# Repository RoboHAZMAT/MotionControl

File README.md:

Motion Control
=============

Code for the intuitive motion control for the robot. This repo contains all of the code needed to use the wearable motion control interface. Main features are the Motion Control Glove code and the IMU sensor reading programs.

###**Directories:**

  - **HandMotionControlOpt:** An optimized version of the code needed to operate the robot hands using the flex sensor based gloves. Takes the voltage drop readings from the flex sensor in the analog pins and relates that to servo motor rotation angles. Has a calibration method for different sized hands with a default setting as well. Green, yellow, and red LED status lights are used. Written for an Arduino Lilypad.

  - **IMUReading:** Contains several library files developed by Jeff Rowberg to deal with reading in the MPU 9150 IMU sensor we are using as well as the DMP. Two versions of IMU reading programs are functional, one which uses the DMP and one that uses the raw gyroscope and accelerometer data along with our custom Kalman Filter.
  
  - **Kalman Filter MATLAB:** Old code written for Dr. Tomonari Furukawa's Bayesian Robotics course implementing a one DOF Kalman Filter for accurate yaw estimates and drift cancelling.
  
  - **Mechtronic Arm:** In progress directory for controlling the Mechatronic Arm in various ways for testing.
  
  - **Tactile Feedback:** In progress directory used for tactile feedback code. The plan is to use a pressure sensor at the tips of the gripper fingers that senses when the gripper is touching an object. The pressure is related so some sort of tactile feedback method, either small inflatable pressure bags on the glove fingers or small vibration motors. 
  
  - **I2CDev:** Added standard library for communication over I2C on Arduino.

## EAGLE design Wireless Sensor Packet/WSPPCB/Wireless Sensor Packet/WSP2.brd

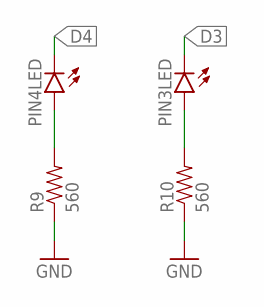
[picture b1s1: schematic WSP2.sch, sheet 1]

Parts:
PIN3LED, PIN4LED: LED0603; LED-0603
R9, R10: 560; 0603-RES

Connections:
D3: PIN3LED.C; also elsewhere on the board
D4: PIN4LED.C; also elsewhere on the board
GND: R9.1, R10.1; also elsewhere on the board
unnamed: PIN4LED.A, R9.2
unnamed: PIN3LED.A, R10.2

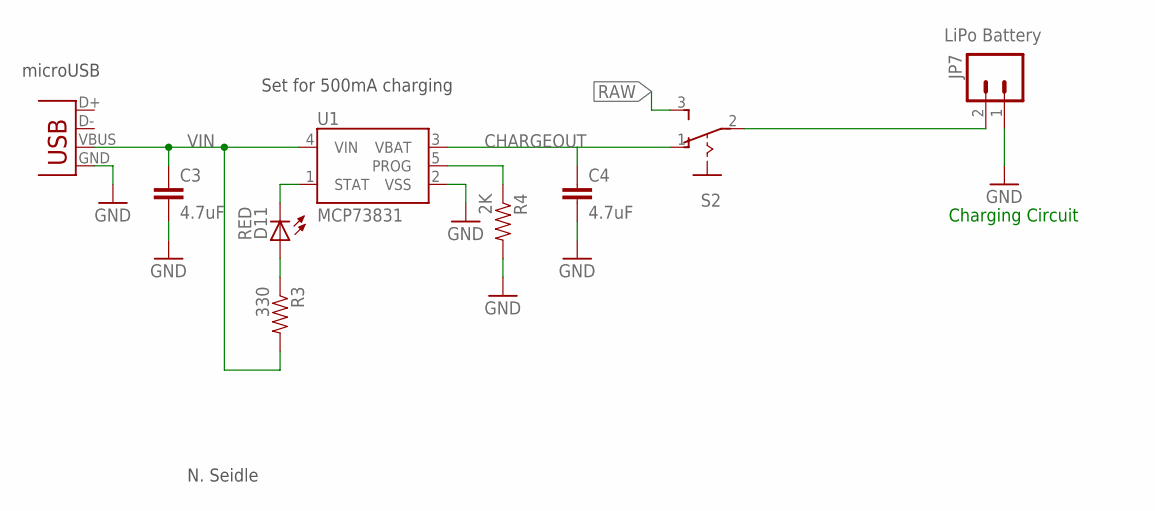
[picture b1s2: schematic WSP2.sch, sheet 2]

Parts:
C3, C4: 4.7uF; 0402-CAP
D11: RED; LED-0603
JP7: LiPo Battery; JST-2-SMD
R3: 330; 0402-RES
R4: 2K; 0402-RES
S2: 255SB
U1: MCP73831; SOT23-5
X1: Micro USB; USB-MICROB

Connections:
CHARGEOUT: C4.1, S2.1 (O), U1.3 (VBAT)
GND: C3.2, C4.2, JP7.1, R4.2, U1.2 (VSS), X1.GND; also elsewhere on the board
unnamed: D11.A, R3.1
POSBAT: JP7.2, S2.2
PROG: R4.1, U1.5 (PROG)
RAW: S2.3 (S); also elsewhere on the board
STAT: D11.C, U1.1 (STAT)
VIN: C3.1, R3.2, U1.4 (VIN), X1.VBUS

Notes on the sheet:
Set for 500mA charging
N. Seidle
microUSB
Charging Circuit

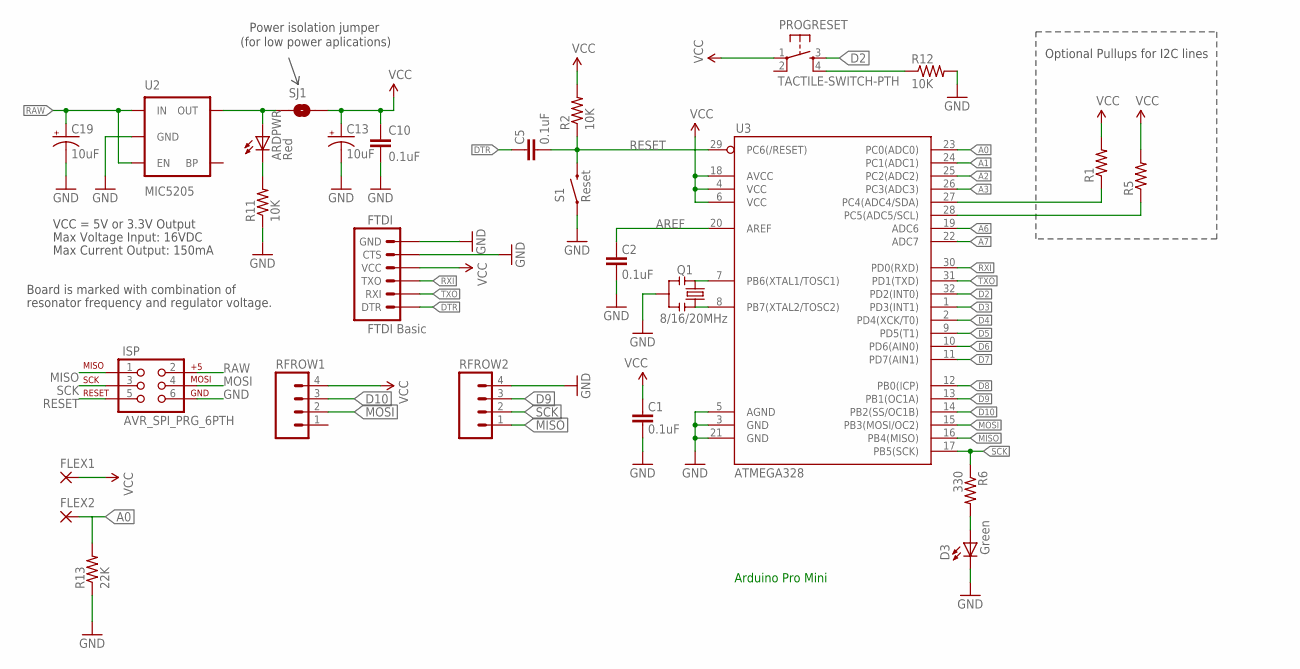
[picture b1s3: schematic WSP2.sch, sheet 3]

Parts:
ARDPWR: Red; 0603-LED-ALT1
C1, C2, C5, C10: 0.1uF; 0603-CAP
C13, C19: 10uF; EIA3216
D3: Green; 0603-LED-ALT1
FLEX1, FLEX2: 1,6/0,9
FTDI: FTDI Basic; 1X06
ISP: AVR_SPI_PRG_6PTH; 2X3
PROGRESET: TACTILE-SWITCH-PTH; TAC-SWITCH-PTH
Q1: 8/16/20MHz; RESONATOR-SMD-1:1
R1, R5: RESISTOR0603-RES; 0603-RES
R2, R11, R12: 10K; 0603-RES
R6: 330; 0603-RES
R13: 22K; 0603-RES
RFROW1, RFROW2: M041.27MM; 1X04-1.27MM
S1: Reset; TACTILE-SWITCH-SMD-ALT01
SJ1: SOLDERJUMPERNC; SJ_2S
U2: MIC5205; SOT23-5
U3: ATMEGA328; TQFP32-08

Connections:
3.3V: FLEX1.1, FTDI.4 (VCC), PROGRESET.1, RFROW1.4
A0: FLEX2.1, R13.2, U3.23 (PC0(ADC0))
A1: U3.24 (PC1(ADC1))
A2: U3.25 (PC2(ADC2))
A3: U3.26 (PC3(ADC3))
A5: R5.1, U3.28 (PC5(ADC5/SCL))
A6: U3.19 (ADC6)
A7: U3.22 (ADC7)
AREF: C2.2, U3.20 (AREF)
D2: PROGRESET.3, U3.32 (PD2(INT0))
D3: U3.1 (PD3(INT1)); also elsewhere on the board
D4: U3.2 (PD4(XCK/T0)); also elsewhere on the board
D5: U3.9 (PD5(T1))
D6: U3.10 (PD6(AIN0))
D7: U3.11 (PD7(AIN1))
D8: U3.12 (PB0(ICP))
D9: RFROW2.3, U3.13 (PB1(OC1A))
D10: RFROW1.3, U3.14 (PB2(SS/OC1B))
DTR: C5.2, FTDI.1 (DTR)
GND: C1.1, C2.1, C10.2, C13.C (-), C19.C (-), D3.C, FTDI.5 (CTS), FTDI.6 (GND), ISP.6, Q1.2, R11.1, R12.2, R13.1, RFROW2.4, S1.1, S1.2 (1), U2.2 (GND), U3.3 (GND), U3.5 (AGND), U3.21 (GND); also elsewhere on the board
MISO: ISP.1, RFROW2.1, U3.16 (PB4(MISO))
MOSI: ISP.4, RFROW1.2, U3.15 (PB3(MOSI/OC2))
unnamed: Q1.3, U3.8 (PB7(XTAL2/TOSC2))
unnamed: Q1.1, U3.7 (PB6(XTAL1/TOSC1))
unnamed: ARDPWR.A, SJ1.1, U2.5 (OUT)
unnamed: ARDPWR.C, R11.2
unnamed: D3.A, R6.2
unnamed: PROGRESET.4, R12.1
RAW: C19.A (+), ISP.2, U2.1 (IN), U2.3 (EN); also elsewhere on the board
RESET: C5.1, ISP.5, R2.1, S1.3 (2), S1.4 (2), U3.29 (PC6(/RESET))
RXI: FTDI.3 (TXO), U3.30 (PD0(RXD))
SCK: ISP.3, R6.1, RFROW2.2, U3.17 (PB5(SCK))
SDA: R1.1, U3.27 (PC4(ADC4/SDA)); also elsewhere on the board
TXO: FTDI.2 (RXI), U3.31 (PD1(TXD))
VCC: C1.2, C10.1, C13.A (+), R1.2, R2.2, R5.2, SJ1.2, U3.4 (VCC), U3.6 (VCC), U3.18 (AVCC); also elsewhere on the board

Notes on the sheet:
Max Voltage Input: 16VDC
Max Current Output: 150mA
Board is marked with combination of
resonator frequency and regulator voltage.
VCC = 5V or 3.3V Output
Optional Pullups for I2C lines
Power isolation jumper
(for low power aplications)
Arduino Pro Mini

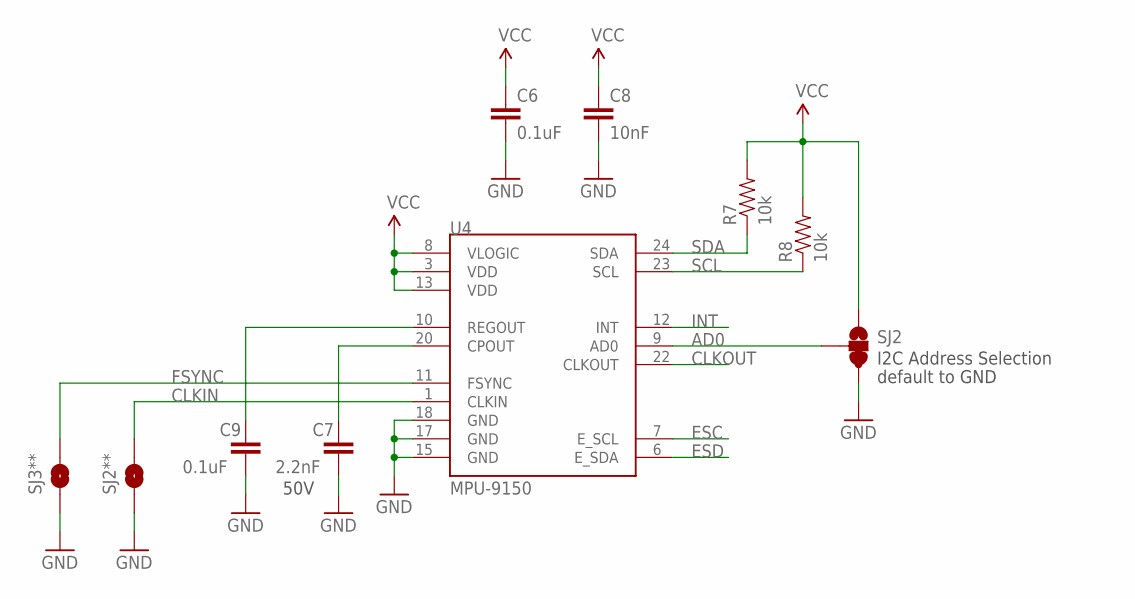
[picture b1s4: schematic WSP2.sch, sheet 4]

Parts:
C6, C9: 0.1uF; 0402-CAP
C7: 2.2nF; 0402-CAP
C8: 10nF; 0402-CAP
R7, R8: 10k; 0402-RES
SJ2: SOLDERJUMPER_2WAYPASTE2&3; SJ_3_PASTE2&3
SJ2**, SJ3**: SOLDERJUMPERTRACE; SJ_2S-TRACE
U4: MPU-9150; QFN-24-NP

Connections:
AD0: SJ2.2, U4.9 (AD0)
CLKIN: SJ2**.2, U4.1 (CLKIN)
CLKOUT: U4.22 (CLKOUT)
ESC: U4.7 (E_SCL)
ESD: U4.6 (E_SDA)
FSYNC: SJ3**.2, U4.11 (FSYNC)
GND: C6.2, C7.2, C8.2, C9.2, SJ2.3, SJ2**.1, SJ3**.1, U4.15 (GND), U4.17 (GND), U4.18 (GND); also elsewhere on the board
INT: U4.12 (INT)
unnamed: C7.1, U4.20 (CPOUT)
unnamed: C9.1, U4.10 (REGOUT)
SCL: R8.1, U4.23 (SCL)
SDA: R7.1, U4.24 (SDA); also elsewhere on the board
VCC: C6.1, C8.1, R7.2, R8.2, SJ2.1, U4.3 (VDD), U4.8 (VLOGIC), U4.13 (VDD); also elsewhere on the board

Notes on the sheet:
50V
I2C Address Selection
default to GND

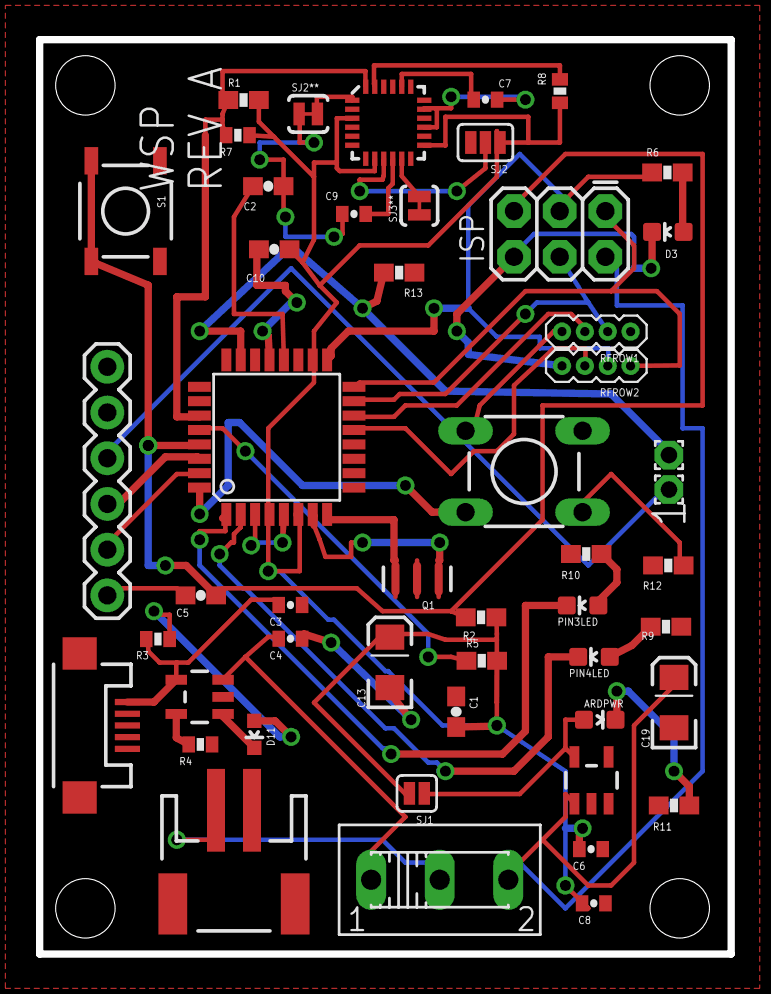
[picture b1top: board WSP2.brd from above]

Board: 2 copper layers, 38.4 x 50.8 mm, 54 parts (0 on the bottom side), 40 nets.

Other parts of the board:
JP1, JP2, JP14, JP15: STAND-OFF

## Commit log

2014-11-11 Create HandMotionControlOpt.ino
    Control for the motion control hand glove.
2014-11-11 Update README.md
    Added a small description of the motion control code.
2014-11-11 HandMotionControlOpt directory
2014-11-11 Update test
2014-11-11 Add John's cleaned up mechatronic arm control code.
2014-11-11 Adds the Kalman Filter IMU code and MATLAB <-> Arduino interface.
2014-11-11 Increase delay to give robot time to move.
2014-11-11 Version update.
2014-11-11 Add description of changes.
2014-11-12 Documentation
2014-11-12 Documentation again.
2014-11-12 Change
2014-11-12 docs
2014-11-12 change to match fork
2014-11-12 test docs
2014-11-15 Extend range on Servos
2014-11-16 Version Adding and Organizing
    Renamed original Mechatronic_Arm.ino to reflect that it uses only
    Trimpots for control. Added new folders with the newer version that uses
    an Uno and a Mega to control the arm via joysticks. This version has LED
    feedback as well.
2014-11-18 Adds support for reading the IMU
    Uses the standard library for reading raw IMU data for the MPU 9150 for
    on github.
2014-11-18 Increases Servo range limitations.
    Changes the maximum range to open gripper since hardware changes were
    made.
2014-11-18 Adding ability to read IMU.
    Forgot to upload the IMU9_Read.m... Now we can actually read the sensor
    data.
2014-11-19 Custom IMU read program
    UNTESTED.
2014-11-19 Adds library for reading quaternions
    UNTESTED
2014-11-19 Documentation and calibration changes
    Adds commenting on the functions and returns calibration value.
2014-11-20 Commenting / program description
    Describes what happens in the program to make it easy for anyone to pick
    up and use the code.
2014-11-24 Working Kalman Filter on the IMU (kinda...)
    The KF works for the IMU in the roll and pitch measurements. Yaw needs
    integration from the magnetometer readings to work. Changed data types
    on some things to make it work.
2014-11-24 Noise removal, data management
    Removes initial measurement noise and also adds smoothing for the
    estimated KF angles. Some commenting and an updated TO TO list.
2014-11-24 Update motion model with position instead of speed
    Use time difference to update motion model
2014-11-25 Mechatronic Arm Update
    Uno
    Configured I2C recieve
    May reconfigure as Master
    Meant to read servo positions in array and write to servos
    Mega
    Testing joysticks
2014-11-27 Mechatronic Arm Test
    Commit before changing I2C code majorly
    I2C not working in current configuration
    No read or write is being initiated
    Attempting different configuration after this commit
2014-12-05 Adds good IMU readings with KF and DMP
    No drift and good fusion.
2014-12-16 Rename folder for clarity
2014-12-16 Changes for use with the arm
    Gets rid of Serial communication (not needed). Adds a default
    calibration in case user forgets to calibrate. Changes LED timings.
    Reverses mapping for servo in arm gripper.
2014-12-16 Updated DMP communication
    Allows bug free reading of the IMU DMP data. Gets rid of arm freak outs
    and issues with buffer overflow.
2014-12-16 Working programs, NOT for use yet.
    Adds Serial test program start and tactile feedback start.
2014-12-16 2 Versions of IMU reading
    Adds 2 different ways to read the IMU data.
    IMUArm uses the DMP
    IMURead uses raw data and a Kalman Filter
2014-12-16 Update README.md
    Adds description of directories
2014-12-16 Clean up Mechatronic Arm directory
2014-12-16 Take out unnecessary file
2014-12-16 Adds John's arm control code
2014-12-25 Adds Quaternion reading support
    Modifies the original IMU code to add support for Quaternion reading and
    output.
2014-12-25 Adds Quaternion reading support (clean)
2015-01-05 Slows down the rate to avoid saturating the buffer
2015-01-06 Documentation and Clean Up
2015-01-15 Processing Sketch to Control Mechatronic Arm
2015-02-04 Long time Ago
2015-02-05 Minor Fix
    Method names were incorrect and thus not being recognized by Arduino
    compiler. Removed "TC" at the end of the method names. Now properly
    compiles. Testing needed to confirm that change is correct & that the
    IMU reads properly.
2015-02-20 Wireless Sensor Packet Initial Commit
    Included is the RF24 library with all necessary files for using the
    nrf24l01+ RF transceivers. The included .ino's are configured for three
    different Arduino boards.
2015-02-20 Wireless Sensor Packet ReadME initial Commit
2015-02-20 Formatting
2015-02-24 Wireless Quaternion Transmit Working
    -Combined and altered many pieces of code
    -Mega serves as receiver in testing
    -Uno was used to test new data structure
    -Nano with IMU transmitted actual readings to Mega successfully
    -Refinement needed to make as smooth, clear and fast as possible at this
    level.
2015-02-25 Wireless Sensor Packet PCB
    Initial Commit
2015-03-02 WSPPCB2
    Updated main file, renamed to WSP2.
2015-03-02 WSPPCB Update
    Created initial component layout for PCB
2015-03-04 Rev A of WSP PCB
2015-03-23 Good things
    -MX64T arbotix-m code
    -cleaned up wireless IMU stuff
    -added intialization checks
2015-04-01 Tested and bug removal
2015-04-16 Just to be safe update
    -Added altered ax12 libraries with new added functions
    -added mx64 arbotix code with setup loop for initializing mx64
    paramters, remove serial debug lines
    -added debug version of pro mini WSP code
    -Changed MegaStarRF to work with Uno, removed debug lines
    -Re-added serial interface for WSP Code to change address
2015-04-20 Minor Updates
    -Addition of debug copies
    -fixed pipes setup (set back to original array)
    -Added/fixed button press reset
2015-04-24 Improvements
    Arbotix Code
    -changed serial so that it might actually work
    -changed feed string to "00!0000" thanks to simplifications
    -uses custom ax12 library, be sure to get one with LED and EEProm lock
    added
    MegaStarRF
2015-05-01 Updates for safety

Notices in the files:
parts and their libraries:
SparkFun-Passives: Licensing: CC v3.0 Share-Alike You are welcome to use this library for commercial purposes.
GeekAmmo: Licensing:Creative Commons ShareAlike 4.0 International - https://creativecommons.org/licenses/by-sa/4.0
